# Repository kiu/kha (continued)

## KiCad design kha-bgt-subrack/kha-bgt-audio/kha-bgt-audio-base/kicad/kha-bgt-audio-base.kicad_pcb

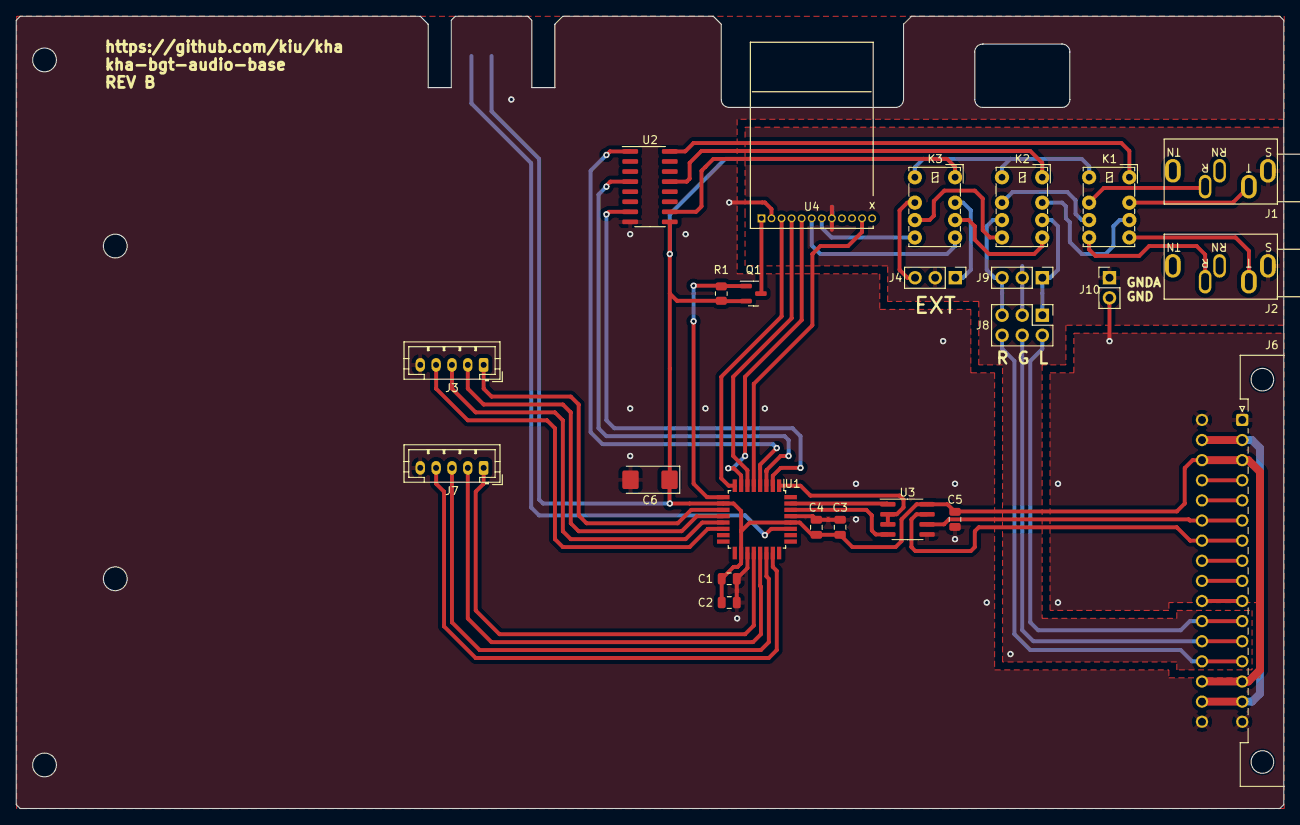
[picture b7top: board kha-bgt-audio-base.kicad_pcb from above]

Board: 2 copper layers, 160.0 x 100.0 mm, 25 parts (1 on the bottom side), 52 nets.

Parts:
C1, C4: 10nF; C_0805_2012Metric
C2, C3, C5: 100nF; C_0805_2012Metric
C6: 220uF; CP_EIA-6032-28_Kemet-C
J1, J2: AudioJack3; PJ-325C5
J3, J7: Conn_01x05; JST_PH_B5B-PH-K_1x05_P2.00mm_Vertical
J4, J9: Conn_01x03; PinHeader_1x03_P2.54mm_Vertical
J5: AVR-UPDI-6; eAVR6-UPDI-F
J6: DIN41612_02x16_AC; DIN41612_C2_2x16_Male_Horizontal_THT
J8: Conn_02x03_Odd_Even; PinHeader_2x03_P2.54mm_Vertical
J10: 1x02_Jumper; PinHeader_1x02_P2.54mm_Vertical
K1, K2, K3: HFD4/5; Relay_DPDT_HDF4-5
Q1: DMG2301L; SOT-23
R1: 10k; R_0805_2012Metric
U1: AVR64DD32; TQFP-32_7x7mm_P0.8mm
U2: ULN2003; SOP-16_3.9x9.9mm_P1.27mm
U3: SP481E; SOIC-8_3.9x4.9mm_P1.27mm
U4: KCX_BT_EMITTER_1.7; KCX_BT_EMITTER_V1.7 12P

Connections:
+5V: C1.1, C2.1, C3.1, C4.1, C5.1, C6.1, J5.2 (VCC), J6.a3, J6.a14, J6.c3, J6.c14, K1.8, K2.8, K3.8, Q1.2 (S), R1.1, U1.10 (VDDIO2), U1.18 (VDD), U1.28 (VDD), U2.9 (COM), U3.8 (VCC)
+12V: J6.a2, J6.a15, J6.c2, J6.c15
AUDIO_LEFT: J8.1, J9.1, K2.3
AUDIO_RIGHT: J8.5, J9.3, K2.6
BTN01: J3.1, U1.11 (PD1)
BTN02: J3.3, U1.13 (PD3)
BTN03: J7.1, U1.20 (XTAL32K1/PF0)
BTN04: J7.3, U1.22 (PF2)
BT_CON: U1.5 (PA7), U4.11 (CON)
BT_LNK: U1.8 (PC2), U4.3 (LINK)
BT_RX: U1.6 (PC0), U4.4 (RX)
BT_TX: U1.7 (PC1), U4.5 (TX)
BT_VCC: Q1.3 (D), U4.1 (+5V)
BUS01: J6.a8, J6.c8
BUS02: J6.a9, J6.c9
BUS03: J6.a10, J6.c10
BUS04: J6.a11, J6.c11, J8.2
BUS05: J6.a12, J6.c12, J8.4
BUS06: J6.a13, J6.c13, J8.6
BUS_DIR: U1.1 (PA3), U3.2 (~RE), U3.3 (DE)
BUS_RX: U1.31 (PA1), U3.1 (RO)
BUS_TX: U1.30 (EXTCLK/PA0), U3.4 (DI)
GND: C1.2, C2.2, C3.2, C4.2, C5.2, C6.2, J3.5, J5.6 (GND), J6.a1, J6.a16, J6.c1, J6.c16, J7.5, J10.2, U1.19 (GND), U1.29 (GND), U2.8 (GND), U3.5 (GND), U4.2 (GND)
GNDA: J1.S, J2.S, J4.2, J8.3, J9.2, J10.1, U4.8 (AGND)
LED01: J3.2, U1.12 (PD2)
LED02: J3.4, U1.14 (PD4)
LED03: J7.2, U1.21 (XTAL32K2/PF1)
LED04: J7.4, U1.23 (PF3)
unnamed: J1.R, K1.7
unnamed: J1.T, K1.2
unnamed: J2.R, K1.5
unnamed: J2.T, K1.4
unnamed: J4.1, K3.2
unnamed: J4.3, K3.7
unnamed: K1.3, K2.2
unnamed: K1.6, K2.7
unnamed: K2.4, K3.3
unnamed: K2.5, K3.6
unnamed: K3.4, U4.6 (LEFT)
unnamed: K3.5, U4.7 (RIGHT)
R01: K1.1, U2.16 (O1)
R02: K3.1, U2.10 (O7)
R03: K2.1, U2.13 (O4)
RS485_A: J6.a6, J6.c6, U3.6 (A)
RS485_B: J6.a7, J6.c7, U3.7 (B)
RS485_INT_A: J6.a4, J6.c4
RS485_INT_B: J6.a5, J6.c5
SR01: U1.4 (PA6), U2.1 (I1)
SR02: U1.2 (PA4), U2.7 (I7)
SR03: U1.3 (PA5), U2.4 (I4)
S_BT_VCC: Q1.1 (G), R1.2, U1.9 (PC3)
UPDI: J5.1 (DATA), U1.27 (PF7/UPDI)

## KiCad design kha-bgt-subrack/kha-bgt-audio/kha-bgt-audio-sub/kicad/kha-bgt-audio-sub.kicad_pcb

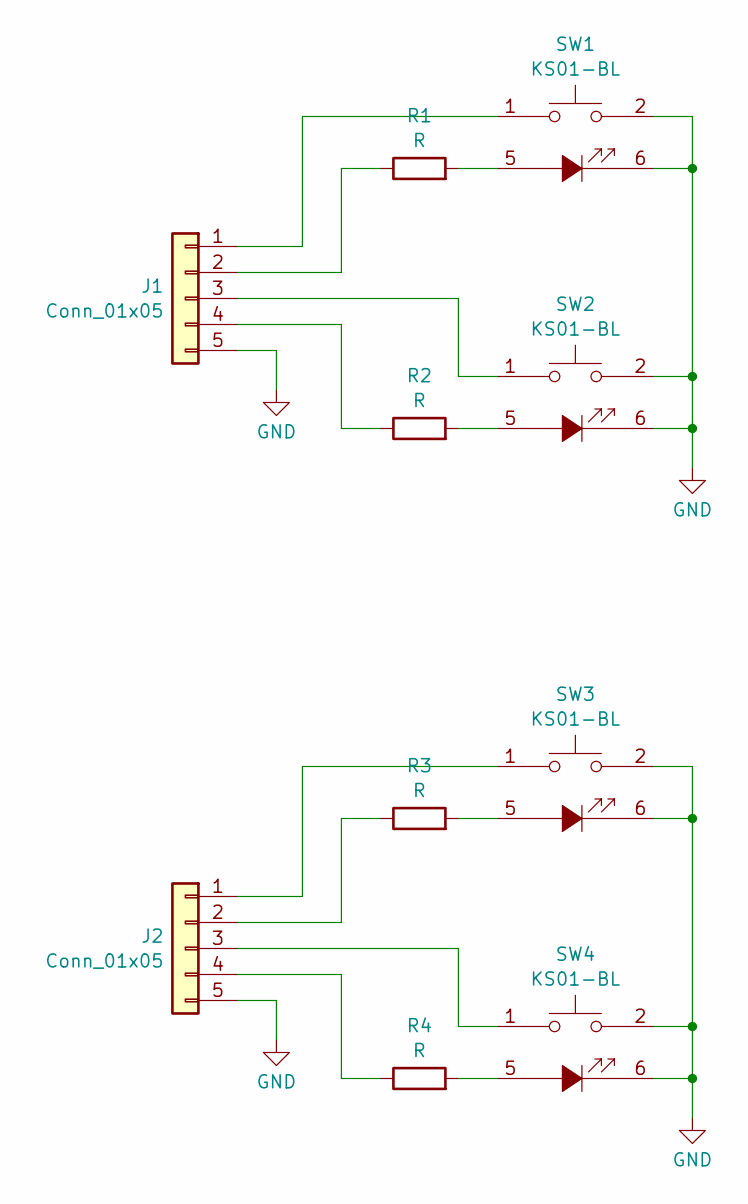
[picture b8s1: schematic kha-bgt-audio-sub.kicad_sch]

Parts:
J1, J2: Conn_01x05; JST_PH_B5B-PH-K_1x05_P2.00mm_Vertical
R1, R2, R3, R4: R; R_0805_2012Metric
SW1, SW2, SW3, SW4: KS01-BL

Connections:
GND: J1.5, J2.5, SW1.2, SW1.6, SW2.2, SW2.6, SW3.2, SW3.6, SW4.2, SW4.6
unnamed: J1.1, SW1.1
unnamed: J1.2, R1.1
unnamed: J1.3, SW2.1
unnamed: J1.4, R2.1
unnamed: J2.1, SW3.1
unnamed: J2.2, R3.1
unnamed: J2.3, SW4.1
unnamed: J2.4, R4.1
unnamed: R1.2, SW1.5
unnamed: R2.2, SW2.5
unnamed: R3.2, SW3.5
unnamed: R4.2, SW4.5

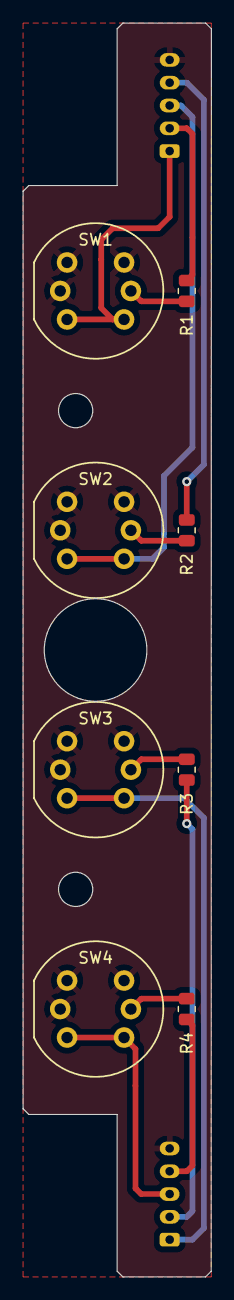
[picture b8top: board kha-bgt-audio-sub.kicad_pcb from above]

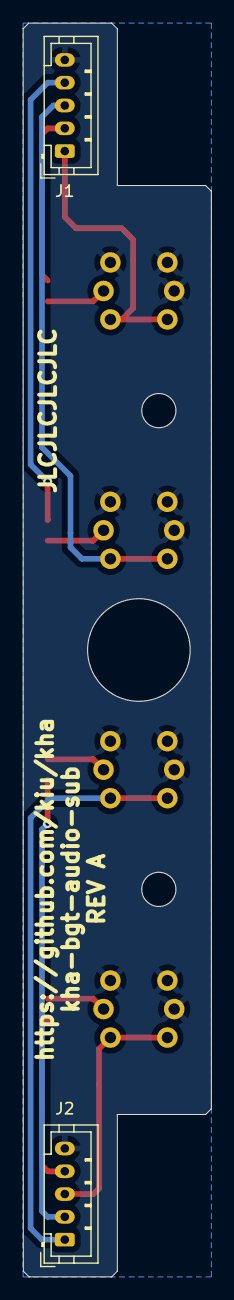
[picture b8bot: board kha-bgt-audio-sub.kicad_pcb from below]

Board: 2 copper layers, 16.5 x 110.0 mm, 10 parts (2 on the bottom side), 13 nets.

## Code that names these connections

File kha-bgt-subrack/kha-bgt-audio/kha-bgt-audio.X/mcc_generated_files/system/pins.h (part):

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
/**
 * @ingroup  pinsdriver
 * @brief Default Interrupt Handler for IO_PA1 pin. 
 *        This is a predefined interrupt handler to be used together with the IO_PA1_SetInterruptHandler() method.
 *        This handler is called every time the IO_PA1 ISR is executed. 
 * @pre PIN_MANAGER_Initialize() has been called at least once
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
/**
 * @ingroup  pinsdriver
 * @brief Interrupt Handler Setter for IO_PA1 pin input-sense-config functionality.
 *        Allows selecting an interrupt handler for IO_PA1 at application runtime
 * @pre PIN_MANAGER_Initialize() has been called at least once
 * @param InterruptHandler function pointer.
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
/**
 * @ingroup  pinsdriver
 * @brief Default Interrupt Handler for IO_PA0 pin. 
 *        This is a predefined interrupt handler to be used together with the IO_PA0_SetInterruptHandler() method.
 *        This handler is called every time the IO_PA0 ISR is executed. 
 * @pre PIN_MANAGER_Initialize() has been called at least once
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
/**
 * @ingroup  pinsdriver
 * @brief Interrupt Handler Setter for IO_PA0 pin input-sense-config functionality.
 *        Allows selecting an interrupt handler for IO_PA0 at application runtime
 * @pre PIN_MANAGER_Initialize() has been called at least once
 * @param InterruptHandler function pointer.
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
/**
 * @ingroup  pinsdriver
 * @brief Default Interrupt Handler for IO_PA3 pin. 
 *        This is a predefined interrupt handler to be used together with the IO_PA3_SetInterruptHandler() method.
 *        This handler is called every time the IO_PA3 ISR is executed. 
 * @pre PIN_MANAGER_Initialize() has been called at least once
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
/**
 * @ingroup  pinsdriver
 * @brief Interrupt Handler Setter for IO_PA3 pin input-sense-config functionality.
 *        Allows selecting an interrupt handler for IO_PA3 at application runtime
 * @pre PIN_MANAGER_Initialize() has been called at least once
 * @param InterruptHandler function pointer.
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
/**
 * @ingroup  pinsdriver
 * @brief Default Interrupt Handler for IO_PC1 pin. 
 *        This is a predefined interrupt handler to be used together with the IO_PC1_SetInterruptHandler() method.
 *        This handler is called every time the IO_PC1 ISR is executed. 
 * @pre PIN_MANAGER_Initialize() has been called at least once
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
/**
 * @ingroup  pinsdriver
 * @brief Interrupt Handler Setter for IO_PC1 pin input-sense-config functionality.
 *        Allows selecting an interrupt handler for IO_PC1 at application runtime
 * @pre PIN_MANAGER_Initialize() has been called at least once
 * @param InterruptHandler function pointer.
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
/**
 * @ingroup  pinsdriver
 * @brief Default Interrupt Handler for IO_PC0 pin. 
 *        This is a predefined interrupt handler to be used together with the IO_PC0_SetInterruptHandler() method.
 *        This handler is called every time the IO_PC0 ISR is executed. 
 * @pre PIN_MANAGER_Initialize() has been called at least once
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
/**
 * @ingroup  pinsdriver
 * @brief Interrupt Handler Setter for IO_PC0 pin input-sense-config functionality.
 *        Allows selecting an interrupt handler for IO_PC0 at application runtime
 * @pre PIN_MANAGER_Initialize() has been called at least once
 * @param InterruptHandler function pointer.
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
/**
 * @ingroup  pinsdriver
 * @brief Default Interrupt Handler for IO_BT_LNK pin. 
 *        This is a predefined interrupt handler to be used together with the IO_BT_LNK_SetInterruptHandler() method.
 *        This handler is called every time the IO_BT_LNK ISR is executed. 
 * @pre PIN_MANAGER_Initialize() has been called at least once
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
/**
 * @ingroup  pinsdriver
 * @brief Interrupt Handler Setter for IO_BT_LNK pin input-sense-config functionality.
 *        Allows selecting an interrupt handler for IO_BT_LNK at application runtime
 * @pre PIN_MANAGER_Initialize() has been called at least once
 * @param InterruptHandler function pointer.
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
/**
 * @ingroup  pinsdriver
 * @brief Default Interrupt Handler for IO_BTN01 pin. 
 *        This is a predefined interrupt handler to be used together with the IO_BTN01_SetInterruptHandler() method.
 *        This handler is called every time the IO_BTN01 ISR is executed. 
 * @pre PIN_MANAGER_Initialize() has been called at least once
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
/**
 * @ingroup  pinsdriver
 * @brief Interrupt Handler Setter for IO_BTN01 pin input-sense-config functionality.
 *        Allows selecting an interrupt handler for IO_BTN01 at application runtime
 * @pre PIN_MANAGER_Initialize() has been called at least once
 * @param InterruptHandler function pointer.
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
/**
 * @ingroup  pinsdriver
 * @brief Default Interrupt Handler for IO_BTN02 pin. 
 *        This is a predefined interrupt handler to be used together with the IO_BTN02_SetInterruptHandler() method.
 *        This handler is called every time the IO_BTN02 ISR is executed. 
 * @pre PIN_MANAGER_Initialize() has been called at least once
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
/**
 * @ingroup  pinsdriver
 * @brief Interrupt Handler Setter for IO_BTN02 pin input-sense-config functionality.
 *        Allows selecting an interrupt handler for IO_BTN02 at application runtime
 * @pre PIN_MANAGER_Initialize() has been called at least once
 * @param InterruptHandler function pointer.
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
/**
 * @ingroup  pinsdriver
 * @brief Default Interrupt Handler for IO_BTN03 pin. 
 *        This is a predefined interrupt handler to be used together with the IO_BTN03_SetInterruptHandler() method.
 *        This handler is called every time the IO_BTN03 ISR is executed. 
 * @pre PIN_MANAGER_Initialize() has been called at least once
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
/**
 * @ingroup  pinsdriver
 * @brief Interrupt Handler Setter for IO_BTN03 pin input-sense-config functionality.
 *        Allows selecting an interrupt handler for IO_BTN03 at application runtime
 * @pre PIN_MANAGER_Initialize() has been called at least once
 * @param InterruptHandler function pointer.
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
/**
 * @ingroup  pinsdriver
 * @brief Default Interrupt Handler for IO_BT_CON pin. 
 *        This is a predefined interrupt handler to be used together with the IO_BT_CON_SetInterruptHandler() method.
 *        This handler is called every time the IO_BT_CON ISR is executed. 
 * @pre PIN_MANAGER_Initialize() has been called at least once
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
/**
 * @ingroup  pinsdriver
 * @brief Interrupt Handler Setter for IO_BT_CON pin input-sense-config functionality.
 *        Allows selecting an interrupt handler for IO_BT_CON at application runtime
 * @pre PIN_MANAGER_Initialize() has been called at least once
 * @param InterruptHandler function pointer.
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
/**
 * @ingroup  pinsdriver
 * @brief Default Interrupt Handler for IO_BT_VCC pin. 
 *        This is a predefined interrupt handler to be used together with the IO_BT_VCC_SetInterruptHandler() method.
 *        This handler is called every time the IO_BT_VCC ISR is executed. 
 * @pre PIN_MANAGER_Initialize() has been called at least once
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
/**
 * @ingroup  pinsdriver
 * @brief Interrupt Handler Setter for IO_BT_VCC pin input-sense-config functionality.
 *        Allows selecting an interrupt handler for IO_BT_VCC at application runtime
 * @pre PIN_MANAGER_Initialize() has been called at least once
 * @param InterruptHandler function pointer.
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
/**
 * @ingroup  pinsdriver
 * @brief Default Interrupt Handler for IO_LED01 pin. 
 *        This is a predefined interrupt handler to be used together with the IO_LED01_SetInterruptHandler() method.
 *        This handler is called every time the IO_LED01 ISR is executed. 
 * @pre PIN_MANAGER_Initialize() has been called at least once
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
/**
 * @ingroup  pinsdriver
 * @brief Interrupt Handler Setter for IO_LED01 pin input-sense-config functionality.
 *        Allows selecting an interrupt handler for IO_LED01 at application runtime
 * @pre PIN_MANAGER_Initialize() has been called at least once
 * @param InterruptHandler function pointer.
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
/**
 * @ingroup  pinsdriver
 * @brief Default Interrupt Handler for IO_LED02 pin. 
 *        This is a predefined interrupt handler to be used together with the IO_LED02_SetInterruptHandler() method.
 *        This handler is called every time the IO_LED02 ISR is executed. 
 * @pre PIN_MANAGER_Initialize() has been called at least once
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
/**
 * @ingroup  pinsdriver
 * @brief Interrupt Handler Setter for IO_LED02 pin input-sense-config functionality.
 *        Allows selecting an interrupt handler for IO_LED02 at application runtime
 * @pre PIN_MANAGER_Initialize() has been called at least once
 * @param InterruptHandler function pointer.
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
/**
 * @ingroup  pinsdriver
 * @brief Default Interrupt Handler for IO_LED03 pin. 
 *        This is a predefined interrupt handler to be used together with the IO_LED03_SetInterruptHandler() method.
 *        This handler is called every time the IO_LED03 ISR is executed. 
 * @pre PIN_MANAGER_Initialize() has been called at least once
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
/**
 * @ingroup  pinsdriver
 * @brief Interrupt Handler Setter for IO_LED03 pin input-sense-config functionality.
 *        Allows selecting an interrupt handler for IO_LED03 at application runtime
 * @pre PIN_MANAGER_Initialize() has been called at least once
 * @param InterruptHandler function pointer.
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
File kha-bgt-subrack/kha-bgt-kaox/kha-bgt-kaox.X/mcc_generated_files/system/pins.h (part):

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
/**
 * @ingroup  pinsdriver
 * @brief Default Interrupt Handler for IO_PA1 pin. 
 *        This is a predefined interrupt handler to be used together with the IO_PA1_SetInterruptHandler() method.
 *        This handler is called every time the IO_PA1 ISR is executed. 
 * @pre PIN_MANAGER_Initialize() has been called at least once
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
/**
 * @ingroup  pinsdriver
 * @brief Interrupt Handler Setter for IO_PA1 pin input-sense-config functionality.
 *        Allows selecting an interrupt handler for IO_PA1 at application runtime
 * @pre PIN_MANAGER_Initialize() has been called at least once
 * @param InterruptHandler function pointer.
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
/**
 * @ingroup  pinsdriver
 * @brief Default Interrupt Handler for IO_PA0 pin. 
 *        This is a predefined interrupt handler to be used together with the IO_PA0_SetInterruptHandler() method.
 *        This handler is called every time the IO_PA0 ISR is executed. 
 * @pre PIN_MANAGER_Initialize() has been called at least once
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
/**
 * @ingroup  pinsdriver
 * @brief Interrupt Handler Setter for IO_PA0 pin input-sense-config functionality.
 *        Allows selecting an interrupt handler for IO_PA0 at application runtime
 * @pre PIN_MANAGER_Initialize() has been called at least once
 * @param InterruptHandler function pointer.
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
/**
 * @ingroup  pinsdriver
 * @brief Default Interrupt Handler for IO_PA3 pin. 
 *        This is a predefined interrupt handler to be used together with the IO_PA3_SetInterruptHandler() method.
 *        This handler is called every time the IO_PA3 ISR is executed. 
 * @pre PIN_MANAGER_Initialize() has been called at least once
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
/**
 * @ingroup  pinsdriver
 * @brief Interrupt Handler Setter for IO_PA3 pin input-sense-config functionality.
 *        Allows selecting an interrupt handler for IO_PA3 at application runtime
 * @pre PIN_MANAGER_Initialize() has been called at least once
 * @param InterruptHandler function pointer.
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
/**
 * @ingroup  pinsdriver
 * @brief Default Interrupt Handler for IO_BTN03 pin. 
 *        This is a predefined interrupt handler to be used together with the IO_BTN03_SetInterruptHandler() method.
 *        This handler is called every time the IO_BTN03 ISR is executed. 
 * @pre PIN_MANAGER_Initialize() has been called at least once
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
/**
 * @ingroup  pinsdriver
 * @brief Interrupt Handler Setter for IO_BTN03 pin input-sense-config functionality.
 *        Allows selecting an interrupt handler for IO_BTN03 at application runtime
 * @pre PIN_MANAGER_Initialize() has been called at least once
 * @param InterruptHandler function pointer.
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
/**
 * @ingroup  pinsdriver
 * @brief Default Interrupt Handler for IO_BTN02 pin. 
 *        This is a predefined interrupt handler to be used together with the IO_BTN02_SetInterruptHandler() method.
 *        This handler is called every time the IO_BTN02 ISR is executed. 
 * @pre PIN_MANAGER_Initialize() has been called at least once
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
/**
 * @ingroup  pinsdriver
 * @brief Interrupt Handler Setter for IO_BTN02 pin input-sense-config functionality.
 *        Allows selecting an interrupt handler for IO_BTN02 at application runtime
 * @pre PIN_MANAGER_Initialize() has been called at least once
 * @param InterruptHandler function pointer.
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
/**
 * @ingroup  pinsdriver
 * @brief Default Interrupt Handler for IO_BTN01 pin. 
 *        This is a predefined interrupt handler to be used together with the IO_BTN01_SetInterruptHandler() method.
 *        This handler is called every time the IO_BTN01 ISR is executed. 
 * @pre PIN_MANAGER_Initialize() has been called at least once
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
/**
 * @ingroup  pinsdriver
 * @brief Interrupt Handler Setter for IO_BTN01 pin input-sense-config functionality.
 *        Allows selecting an interrupt handler for IO_BTN01 at application runtime
 * @pre PIN_MANAGER_Initialize() has been called at least once
 * @param InterruptHandler function pointer.
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
/**
 * @ingroup  pinsdriver
 * @brief Default Interrupt Handler for IO_PC3 pin. 
 *        This is a predefined interrupt handler to be used together with the IO_PC3_SetInterruptHandler() method.
 *        This handler is called every time the IO_PC3 ISR is executed. 
 * @pre PIN_MANAGER_Initialize() has been called at least once
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
/**
 * @ingroup  pinsdriver
 * @brief Interrupt Handler Setter for IO_PC3 pin input-sense-config functionality.
 *        Allows selecting an interrupt handler for IO_PC3 at application runtime
 * @pre PIN_MANAGER_Initialize() has been called at least once
 * @param InterruptHandler function pointer.
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
/**
 * @ingroup  pinsdriver
 * @brief Default Interrupt Handler for IO_LED03A pin. 
 *        This is a predefined interrupt handler to be used together with the IO_LED03A_SetInterruptHandler() method.
 *        This handler is called every time the IO_LED03A ISR is executed. 
 * @pre PIN_MANAGER_Initialize() has been called at least once
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
/**
 * @ingroup  pinsdriver
 * @brief Interrupt Handler Setter for IO_LED03A pin input-sense-config functionality.
 *        Allows selecting an interrupt handler for IO_LED03A at application runtime
 * @pre PIN_MANAGER_Initialize() has been called at least once
 * @param InterruptHandler function pointer.
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
/**
 * @ingroup  pinsdriver
 * @brief Default Interrupt Handler for IO_LED03B pin. 
 *        This is a predefined interrupt handler to be used together with the IO_LED03B_SetInterruptHandler() method.
 *        This handler is called every time the IO_LED03B ISR is executed. 
 * @pre PIN_MANAGER_Initialize() has been called at least once
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
/**
 * @ingroup  pinsdriver
 * @brief Interrupt Handler Setter for IO_LED03B pin input-sense-config functionality.
 *        Allows selecting an interrupt handler for IO_LED03B at application runtime
 * @pre PIN_MANAGER_Initialize() has been called at least once
 * @param InterruptHandler function pointer.
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
/**
 * @ingroup  pinsdriver
 * @brief Default Interrupt Handler for IO_LED02A pin. 
 *        This is a predefined interrupt handler to be used together with the IO_LED02A_SetInterruptHandler() method.
 *        This handler is called every time the IO_LED02A ISR is executed. 
 * @pre PIN_MANAGER_Initialize() has been called at least once
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
/**
 * @ingroup  pinsdriver
 * @brief Interrupt Handler Setter for IO_LED02A pin input-sense-config functionality.
 *        Allows selecting an interrupt handler for IO_LED02A at application runtime
 * @pre PIN_MANAGER_Initialize() has been called at least once
 * @param InterruptHandler function pointer.
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
/**
 * @ingroup  pinsdriver
 * @brief Default Interrupt Handler for IO_LED02B pin. 
 *        This is a predefined interrupt handler to be used together with the IO_LED02B_SetInterruptHandler() method.
 *        This handler is called every time the IO_LED02B ISR is executed. 
 * @pre PIN_MANAGER_Initialize() has been called at least once
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
/**
 * @ingroup  pinsdriver
 * @brief Interrupt Handler Setter for IO_LED02B pin input-sense-config functionality.
 *        Allows selecting an interrupt handler for IO_LED02B at application runtime
 * @pre PIN_MANAGER_Initialize() has been called at least once
 * @param InterruptHandler function pointer.
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
/**
 * @ingroup  pinsdriver
 * @brief Default Interrupt Handler for IO_LED01A pin. 
 *        This is a predefined interrupt handler to be used together with the IO_LED01A_SetInterruptHandler() method.
 *        This handler is called every time the IO_LED01A ISR is executed. 
 * @pre PIN_MANAGER_Initialize() has been called at least once
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
/**
 * @ingroup  pinsdriver
 * @brief Interrupt Handler Setter for IO_LED01A pin input-sense-config functionality.
 *        Allows selecting an interrupt handler for IO_LED01A at application runtime
 * @pre PIN_MANAGER_Initialize() has been called at least once
 * @param InterruptHandler function pointer.
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
/**
 * @ingroup  pinsdriver
 * @brief Default Interrupt Handler for IO_LED01B pin. 
 *        This is a predefined interrupt handler to be used together with the IO_LED01B_SetInterruptHandler() method.
 *        This handler is called every time the IO_LED01B ISR is executed. 
 * @pre PIN_MANAGER_Initialize() has been called at least once
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
/**
 * @ingroup  pinsdriver
 * @brief Interrupt Handler Setter for IO_LED01B pin input-sense-config functionality.
 *        Allows selecting an interrupt handler for IO_LED01B at application runtime
 * @pre PIN_MANAGER_Initialize() has been called at least once
 * @param InterruptHandler function pointer.
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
